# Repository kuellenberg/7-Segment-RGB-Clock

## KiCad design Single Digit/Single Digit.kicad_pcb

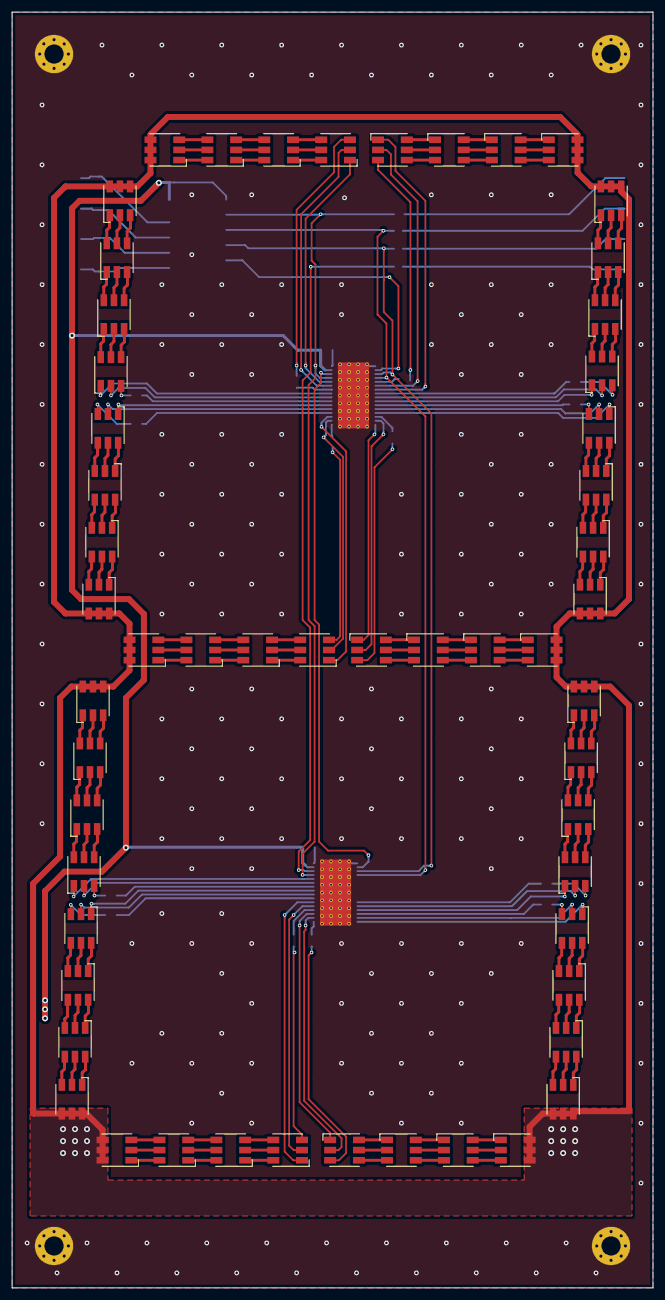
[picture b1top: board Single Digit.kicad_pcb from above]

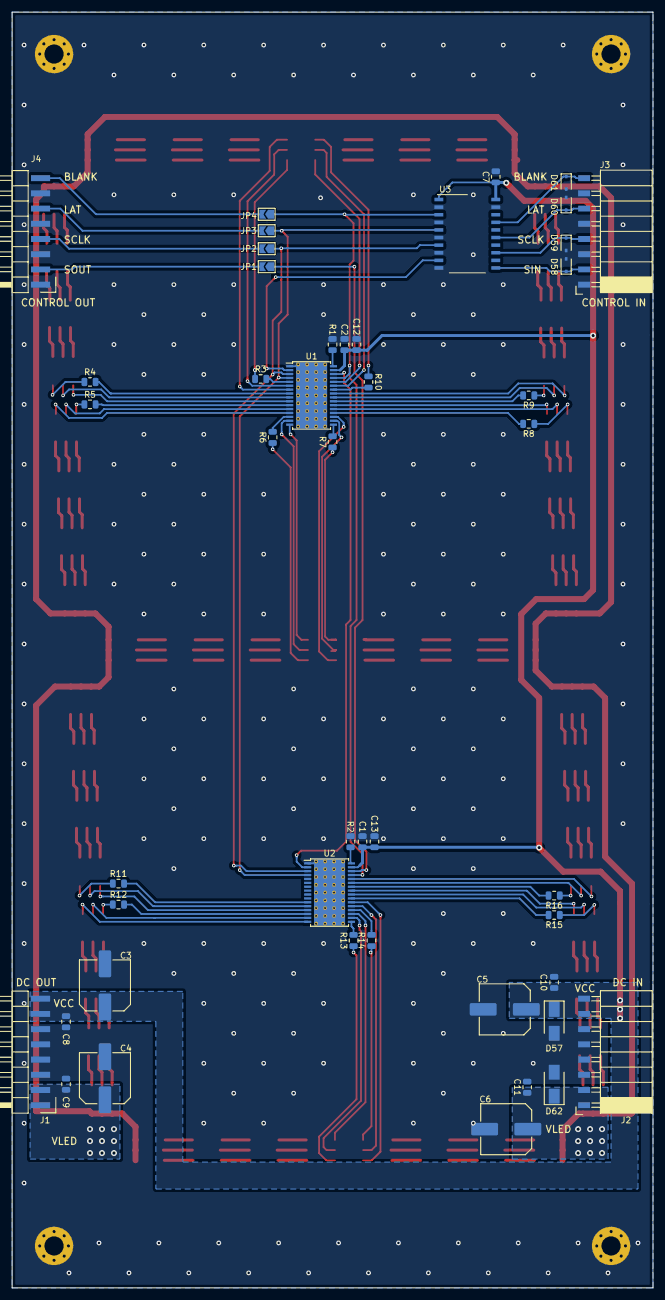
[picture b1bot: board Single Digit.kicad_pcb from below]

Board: 2 copper layers, 107.0 x 213.0 mm, 106 parts (46 on the bottom side), 201 nets.

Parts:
C1, C2, C7, C8, C9, C10, C11: 100n; C_0805_2012Metric
C3, C4, C5, C6: 330uF; C_Elec_8x10.2
C12, C13: 10uF; C_0805_2012Metric
D1, D2, D3, D4, D5, D6, D7, D8, D9, D10, D11, D12, D13, D14, D15, D16, D17, D18, D19, D20, D21, D22, D23, D24, D25, D26, D27, D28, D29, D30, D31, D32, D33, D34, D35, D36, D37, D38, D39, D40, D41, D42, D43, D44, D45, D46, D47, D48, D49, D50, D51, D52, D53, D54, D55, D56: LED_RGB; LED_RGB_5050-6
D57, D62: D_TVS; D_SMA
D58, D59, D60, D61: 5V; D_SOD-323
H1, H2, H3, H4: MountingHole_Pad; MountingHole_3.2mm_M3_Pad_Via
J1: Power In; HARWIN_M20-8890845
J2: Power out; HARWIN_M20-7910842R
J3: Signal in; HARWIN_M20-7910842R
J4: Signal out; HARWIN_M20-8890845
JP1, JP2, JP3, JP4: SolderJumper_2_Open; SolderJumper-2_P1.3mm_Open_TrianglePad1.0x1.5mm
R1, R2, R3, R4, R5, R6, R7, R8, R9, R10, R11, R12, R13, R14, R15, R16: R_Small; R_0805_2012Metric
U1, U2: TLC5952; HTSSOP-32-1EP_6.1x11mm_P0.65mm_EP5.2x11mm_Mask4.11x4.36mm_T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
U3: 74LS244; SO-20_12.8x7.5mm_P1.27mm

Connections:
/BLANK: JP4.1, U1.29, U2.29, U3.3
/LAT: JP3.1, U1.4, U2.4, U3.5
/SCLK: JP2.1, U1.3, U2.3, U3.7
/SIN: U1.2, U3.9
/SOUT: JP1.1, U2.30
/SOUT_TO_SIN: U1.30, U2.2
GND: C1.2, C2.2, C3.2, C4.2, C5.2, C6.2, C7.2, C8.2, C9.2, C10.2, C11.2, C12.2, C13.2, D57.2, D58.2, D59.2, D60.2, D61.2, D62.2, H1.1, H2.1, H3.1, H4.1, J1.3, J1.4, J1.5, J1.6, J2.3, J2.4, J2.5, J2.6, J3.1, J3.3, J3.5, J3.7, J4.1, J4.3, J4.5, J4.7, R1.2, R2.2, U1.1, U1.33, U2.1, U2.33, U3.2, U3.4, U3.6, U3.8, U3.10, U3.19
unnamed: D1.1, U1.7
unnamed: D1.2, U1.6
unnamed: D1.3, R3.1
unnamed: D1.4, D2.3
unnamed: D1.5, D2.2
unnamed: D1.6, D2.1
unnamed: D2.4, D3.3
unnamed: D2.5, D3.2
unnamed: D2.6, D3.1
unnamed: D3.4, D4.3
unnamed: D3.5, D4.2
unnamed: D3.6, D4.1
unnamed: D5.1, U2.13
unnamed: D5.2, U2.12
unnamed: D5.3, R11.1
unnamed: D5.4, D6.3
unnamed: D5.5, D6.2
unnamed: D5.6, D6.1
unnamed: D6.4, D7.3
unnamed: D6.5, D7.2
unnamed: D6.6, D7.1
unnamed: D7.4, D8.3
unnamed: D7.5, D8.2
unnamed: D7.6, D8.1
unnamed: D9.1, U1.10
unnamed: D9.2, U1.9
unnamed: D9.3, R4.1
unnamed: D9.6, D10.1
unnamed: D9.5, D10.2
unnamed: D9.4, D10.3
unnamed: D10.4, D11.3
unnamed: D10.5, D11.2
unnamed: D10.6, D11.1
unnamed: D11.4, D12.3
unnamed: D11.5, D12.2
unnamed: D11.6, D12.1
unnamed: D13.1, U2.16
unnamed: D13.2, U2.15
unnamed: D13.3, R12.1
unnamed: D13.4, D14.3
unnamed: D13.5, D14.2
unnamed: D13.6, D14.1
unnamed: D14.4, D15.3
unnamed: D14.5, D15.2
unnamed: D14.6, D15.1
unnamed: D15.4, D16.3
unnamed: D15.5, D16.2
unnamed: D15.6, D16.1
unnamed: D17.1, U1.13
unnamed: D17.2, U1.12
unnamed: D17.3, R5.1
unnamed: D17.4, D18.3
unnamed: D17.5, D18.2
unnamed: D17.6, D18.1
unnamed: D18.4, D19.3
unnamed: D18.5, D19.2
unnamed: D18.6, D19.1
unnamed: D19.4, D20.3
unnamed: D19.5, D20.2
unnamed: D19.6, D20.1
unnamed: D21.1, U2.19
unnamed: D21.2, U2.18
unnamed: D21.3, R13.1
unnamed: D21.4, D22.3
unnamed: D21.5, D22.2
unnamed: D21.6, D22.1
unnamed: D22.4, D23.3
unnamed: D22.5, D23.2
unnamed: D22.6, D23.1
unnamed: D23.4, D24.3
unnamed: D23.5, D24.2
unnamed: D23.6, D24.1
unnamed: D25.1, U1.16
unnamed: D25.2, U1.15
unnamed: D25.3, R6.1
unnamed: D25.4, D26.3
unnamed: D25.5, D26.2
unnamed: D25.6, D26.1
unnamed: D26.4, D27.3
unnamed: D26.5, D27.2
unnamed: D26.6, D27.1
unnamed: D27.4, D28.3
unnamed: D27.5, D28.2
unnamed: D27.6, D28.1
unnamed: D29.1, U2.22
unnamed: D29.2, U2.21
unnamed: D29.3, R14.1
unnamed: D29.4, D30.3
unnamed: D29.5, D30.2
unnamed: D29.6, D30.1
unnamed: D30.4, D31.3
unnamed: D30.5, D31.2
unnamed: D30.6, D31.1
unnamed: D31.4, D32.3
unnamed: D31.5, D32.2
unnamed: D31.6, D32.1
unnamed: D33.1, U1.19
unnamed: D33.2, U1.18
unnamed: D33.3, R7.1
unnamed: D33.4, D34.3
unnamed: D33.5, D34.2
unnamed: D33.6, D34.1
unnamed: D34.4, D35.3
unnamed: D34.5, D35.2
unnamed: D34.6, D35.1
unnamed: D35.4, D36.3
unnamed: D35.5, D36.2
unnamed: D35.6, D36.1
unnamed: D37.1, U2.25
unnamed: D37.2, U2.24
unnamed: D37.3, R15.1
unnamed: D37.4, D38.3
unnamed: D37.5, D38.2
unnamed: D37.6, D38.1
unnamed: D38.4, D39.3
unnamed: D38.5, D39.2
unnamed: D38.6, D39.1
unnamed: D39.4, D40.3
unnamed: D39.5, D40.2
unnamed: D39.6, D40.1
unnamed: D41.1, U1.22
unnamed: D41.2, U1.21
unnamed: D41.3, R8.1
unnamed: D41.4, D42.3
unnamed: D41.5, D42.2
unnamed: D41.6, D42.1
unnamed: D42.4, D43.3
unnamed: D42.5, D43.2
unnamed: D42.6, D43.1
unnamed: D43.4, D44.3
unnamed: D43.5, D44.2
unnamed: D43.6, D44.1
unnamed: D45.1, U2.28
unnamed: D45.2, U2.27
unnamed: D45.3, R16.1
unnamed: D45.4, D46.3
unnamed: D45.5, D46.2
unnamed: D45.6, D46.1
unnamed: D46.4, D47.3
unnamed: D46.5, D47.2
unnamed: D46.6, D47.1
unnamed: D47.4, D48.3
unnamed: D47.5, D48.2
unnamed: D47.6, D48.1
unnamed: D49.1, U1.25
unnamed: D49.2, U1.24
unnamed: D49.3, R9.1
unnamed: D49.4, D50.3
unnamed: D49.5, D50.2
unnamed: D49.6, D50.1
unnamed: D50.4, D51.3
unnamed: D50.5, D51.2
unnamed: D50.6, D51.1
unnamed: D51.4, D52.3
unnamed: D51.5, D52.2
unnamed: D51.6, D52.1
unnamed: D53.1, U1.28
unnamed: D53.2, U1.27
unnamed: D53.3, R10.1
unnamed: D53.4, D54.3
unnamed: D53.5, D54.2
unnamed: D53.6, D54.1
unnamed: D54.4, D55.3
unnamed: D54.5, D55.2
unnamed: D54.6, D55.1
unnamed: D55.4, D56.3
unnamed: D55.5, D56.2
unnamed: D55.6, D56.1
unnamed: D58.1, J3.2, U3.11
unnamed: D59.1, J3.4, U3.13
unnamed: D60.1, J3.6, U3.15
unnamed: D61.1, J3.8, U3.17
unnamed: J4.2, JP1.2
unnamed: J4.4, JP2.2
unnamed: J4.6, JP3.2
unnamed: J4.8, JP4.2
unnamed: R1.1, U1.32
unnamed: R2.1, U2.32
unnamed: R3.2, U1.5
unnamed: R4.2, U1.8
unnamed: R5.2, U1.11
unnamed: R6.2, U1.14
unnamed: R7.2, U1.17
unnamed: R8.2, U1.20
unnamed: R9.2, U1.23
unnamed: R10.2, U1.26
unnamed: R11.2, U2.11
unnamed: R12.2, U2.14
unnamed: R13.2, U2.17
unnamed: R14.2, U2.20
unnamed: R15.2, U2.23
unnamed: R16.2, U2.26
VCC: C1.1, C2.1, C3.1, C5.1, C7.1, C8.1, C10.1, C12.1, C13.1, D57.1, J1.7, J1.8, J2.7, J2.8, U1.31, U2.31, U3.1, U3.20
Vdrive: C4.1, C6.1, C9.1, C11.1, D4.4, D4.5, D4.6, D8.4, D8.5, D8.6, D12.4, D12.5, D12.6, D16.4, D16.5, D16.6, D20.4, D20.5, D20.6, D24.4, D24.5, D24.6, D28.4, D28.5, D28.6, D32.4, D32.5, D32.6, D36.4, D36.5, D36.6, D40.4, D40.5, D40.6, D44.4, D44.5, D44.6, D48.4, D48.5, D48.6, D52.4, D52.5, D52.6, D56.4, D56.5, D56.6, D62.1, J1.1, J1.2, J2.1, J2.2
